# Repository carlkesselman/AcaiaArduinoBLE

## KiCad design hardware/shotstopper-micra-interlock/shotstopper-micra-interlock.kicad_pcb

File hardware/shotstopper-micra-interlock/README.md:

# ShotStopper Micra Interlock

A replacement for the ShotStopper V3.1 board that gives a La Marzocco Linea
Micra Linea Mini-style brew-by-weight:

- Paddle **on**: the shot starts, and the scale tares and starts its timer.
- Target weight reached: the shot **stops even though the paddle is still on**.
- Paddle **off** at any time: the shot stops, as on a stock machine.
- After an automatic stop, the next shot needs the paddle turned off and on again.
- If the board is unpowered, unplugged from the scale, or crashed, the paddle
  works exactly like a stock Micra.

Status: **design only.** The board has not been built and the firmware has
not run on hardware. Work through [Before you order](#before-you-order) first.

## Same as V3.1

- **Outline and mounting holes**, so it fits the V3.1 case and the same spot in
  the machine.
- **The ESP32-C3 section** at V3.1's pad positions: ESP32-C3-WROOM-02 module
  (antenna over the cut-out), USB-C for power and flashing, BOOT and RESET
  buttons, and the same RGB LED (MEIHUA MHP5050RGBDT) on the same pins (red
  GPIO21, green GPIO20, blue GPIO10), so the indicator colours are unchanged.
- **The connectors and cables.** J3 and J4 are 4-pin headers in the same holes
  V3.1 uses for the Micra (the middle four of the 2x8 pattern's even row, ribbon
  pins 6, 8, 10, 12). The install is the same unplug/plug:
  - **J3 "Buttons"**: the Micra's own paddle plug.
  - **J4 "Brain"**: the black/yellow cable to **CN9** on the control board.
  - **J7 "PWR"**: the red/black cable from **CN4** (+5 V). J7 is turned 90°
    compared with V3.1's power header: pins side by side, + on the left, latch
    wall toward the board edge.

  Pin 1 (square pad, marked BLK) is common, the black wire. Pin 4 is the paddle
  line: the white wire on J3 (marked WHT) and the yellow wire on J4 (marked
  YEL). This is the pin order of the V3.1 Micra kit, checked against V3.1's
  drill file and photos of both sides of a V3.1 board: its 4-pin headers sit
  in the row without the square pad, in holes 3 to 6 counted from the
  square-pad end, with black at hole 3.
  Pins 2 and 3 (CN9 keys the Micra doesn't use) pass straight through.

Removed from V3.1: the Q1 optocoupler ("induce" and "detect"), the SB1–SB5
jumpers, the spade terminals and the reed-switch header. There is no remote
start.

## How it works

Full schematic: [schematic.svg](schematic.svg) (drawn by `schematic.py`; the
netlist itself is in `design.py`).

```
 J3 pin 4 (paddle) ── PADDLE ───[ K1 normally-closed ]─── BRAIN ── J4 pin 4 (to CN9)
                        │
                        └──|<── D4 ── U1 LED ── R10 ── ISO 5V ┐
                                     (R12 across LED)          PS1 isolated DC-DC
 J3/J4 pin 1 (COMMON) ────────────────────────────── ISO 0V ┘   5 V → 5 V
                                                                    (R11 min load)
 GPIO5 ── R1 ── K1 LED            HIGH = K1 open = machine sees paddle off
       └─ R9 10k to GND           keeps K1 closed during boot / reset
 GPIO8 ── U1 transistor to GND    LOW = paddle on  (R13 47k pull-up)
```

- **K1** (CPC1117N) is a normally-closed solid-state switch in series with the
  paddle line. Driving GPIO5 high opens it, so the control board sees the paddle
  as off and stops the shot. With no drive, it is closed.
- **U1** senses the paddle independently of K1. A small isolated 5 V supply
  (PS1) pushes about 1.4 mA through U1's LED and D4 into the paddle wire. When
  the paddle shorts that wire to COMMON, U1 conducts and pulls GPIO8 low. This
  works with K1 open or closed, so the firmware always knows where the paddle is.
- **D4** stops the control board's own pull-up from feeding back into the sense
  circuit. **R10** (2.2 kΩ) sets the sense current and limits what this branch
  could ever push into the control board's input. **R12** (100 kΩ) keeps U1's
  LED off on leakage alone. R12 must stay high: with a low value, a shorted D4
  on an unpowered board would pull the paddle line low through R12, R10 and
  R11, and the machine would brew with the paddle off.
- **R11** (220 Ω, 1206) draws about 21 mA so that PS1 has its 10 % minimum load. With
  less, its output is unspecified and can rise well above 5 V.
- The ESP32 side and the machine side share no copper. They connect only
  through K1, U1 and PS1. The minimum copper gap between the two sides is
  0.8 mm (between PS1's own pins). That is **functional isolation for a
  low-voltage paddle line, not mains-rated isolation.**
- Power: 5 V from CN4 comes in through a resettable fuse (F1, 0.5 A) and D5,
  and USB 5 V through D1. Neither source back-feeds the other, a reversed J7
  does no damage, and a fault on this board cannot draw more than the fuse
  allows from the machine's supply. The shared rail (about 4.6 V) feeds the
  3.3 V regulator (U2).
- PS1 (B0505S-1WR3, 5 V in, 5 V out) is fed from J7 only, through D6. **On USB
  power alone the paddle sensing is off**, so the board can never drive the
  control board's paddle input while the machine is off. PS1 is not on the
  3.3 V rail, which keeps its load, and heat, off the small regulator.
- **D7** (6.2 V zener) clamps the isolated rail in case PS1 ever runs unloaded.

### What the machine's control board sees

- Paddle off: the sense circuit is behind D4, which is reverse-biased by the
  control board's own 5 V pull-up, so nothing flows into or out of the paddle
  input. The isolated rail (4.6–5.5 V, 6.5 V at most with D7) minus D4's drop
  stays at or below the control board's 5 V in normal operation; at the top of
  that range a few microamps can flow through R12 (under 30 mV on a 10 k
  pull-up).
- Paddle on: the sense current (about 1.4 mA) flows from PS1 through the paddle
  switch and back to PS1 on this board. None of it flows in the CN9 cable.
- K1 adds at most 16 Ω in series (8 mV at the measured 0.5 mA) when closed and
  about 1 µA of leakage when open.
- Board unpowered or J7 unplugged: PS1 is off, D4 blocks, K1 is closed. The
  paddle line is as on a stock machine.
- Extra load on CN4: PS1 draws about 35-40 mA from the machine's 5 V, on top
  of the ESP32's draw that V3.1 already has (about 125-140 mA in total, with
  peaks near 400 mA only during WiFi updates).

### If something on this board fails

Worked through for every part (open and short). What the machine can see:

| Fault | Effect on the machine |
|---|---|
| K1 fails open, or GPIO5 stuck high | Never brews until fixed or the board is bypassed. Nothing is damaged |
| K1 fails shorted, K1 drive open | No automatic stop; the paddle still starts and stops |
| U1, R10 or D4 open | No paddle sensing: stock behaviour, no automatic stop |
| R13 open | None: the firmware also enables the ESP32's internal pull-up on GPIO8 |
| U1's output shorted, GPIO8 stuck low | Firmware sees "paddle on" for ever, stops at 90 s and holds: never brews |
| D4 shorted | Board powered: no effect. Board unpowered: input stays above 4.5 V (R12), no brew |
| R11 open | Isolated rail rises to D7's 6.2-6.6 V; at most about 40 µA reaches the input, under 5.4 V |
| C3, C8 or PS1 shorted | F1 limits the current from CN4; the board goes dead, the machine behaves as stock |
| J4 header or cable fitted reversed | **Machine brews as soon as it is powered**, and about 0.6 mA is pulled out of the input. Caught by the bench check below, before the board goes in |
| J3 and J4 plugs swapped | Works by hand; the first automatic stop restarts within 0.3 s, the firmware detects it and disables the interlock (fast white blink) |
| J7 fitted reversed | Board dead (D5, D6 block). Do not connect USB in that state |

The control board's input circuit is not known. Limits above are for an input
with protection diodes to its 5 V and ground, or behind a series resistor.

GPIO8 is V3.1's "IN" pin. V3.1's "OUT" (GPIO6, remote start) is not connected.

GPIO8 is also an ESP32-C3 boot-mode pin: to enter the bootloader with the BOOT
button, have the paddle **off**. Normal start-up is not affected.

## Firmware

Build and flash with PlatformIO from the repo root: `pio run -t upload` (the
`micra` environment sets `MOMENTARY false` and `PADDLE_INTERLOCK true` for the
ESP32-C3). In the Arduino IDE, set those two in
`examples/shotStopper/shotStopper.ino` and pick an ESP32-C3 board with
"USB CDC On Boot" enabled.

What the firmware does in this mode:

| Event | Result |
|-------|--------|
| Paddle on | Machine brews; the shot is tracked: tare, reset and start the timer |
| Predicted target weight, or `MAX_SHOT_DURATION_S` | GPIO5 high: K1 opens and the shot stops |
| Paddle still on after the stop | K1 stays open; no new shot |
| Paddle off for 0.3 s (`PADDLE_DEBOUNCE_MS`) | GPIO5 low: K1 closes, so the next paddle-on always brews. Done from a 5 ms timer, so it does not wait for Bluetooth |
| Paddle off before the target | Shot stops; K1 never opens |
| Scale lost during a weighed shot | GPIO5 high: the shot stops (`STOP_ON_SCALE_LOSS`; set it `false` to leave the shot to the paddle) |
| Scale not connected when the paddle goes on | K1 stays closed; the paddle works by hand |
| Paddle on for `INTERLOCK_MAX_BREW_S` (90 s), with or without a scale | GPIO5 high: the brew stops until the paddle is off |
| Cup lifted or scale knocked for 5 s during a weighed shot (`READINGS_LOST_S`) | Treated like a lost scale: the shot stops |
| Scale connects partway through a shot | Within 5 s of paddle-on the shot is tared and weighed; later than that it is left to the paddle |
| Crash or watchdog reset during a held stop | K1 closes for the fraction of a second the ESP32 takes to restart (the machine may click on briefly), then the stop is held again until the paddle is off |
| Crash or watchdog reset during a weighed shot | The shot is stopped at restart and held until the paddle is off: nothing is weighing it any more |
| Board keeps resetting with the paddle on | The 90 s limit counts across resets |
| `loop()` stalls for 20 s (`WATCHDOG_S`) | The watchdog resets the board. A held stop is still released by the timer meanwhile |
| Paddle reads off right after a stop, then on again | Plugs look swapped: interlock disabled until restart, fast white blink |

### Fail-safe guarantees

- **Paddle off always stops brewing.** This is enforced by hardware: K1 is in
  series, so an open paddle opens the line whatever the ESP32 does.
- **Board unpowered, unplugged, or held in reset.** K1 is normally closed, and R9
  keeps it closed while GPIO5 is undriven, so the Micra behaves as stock.
- **Paddle on starts brewing** whenever the firmware is running, or the board is
  off or resetting. The only time it doesn't is an automatic stop being held,
  and that hold ends once the paddle has read off for 0.3 s. The release runs
  from a timer, independently of `loop()`, so a stalled Bluetooth call cannot
  delay it; a hung `loop()` is reset by the watchdog within `WATCHDOG_S`.
  After an automatic stop, leave the paddle off for at least a third of a
  second before turning it on again.
- **An automatic stop opens K1 first**, before any Bluetooth traffic or
  logging, so a failed link cannot delay it.
- **No remote start.** The ESP32 can only interrupt the paddle line. It cannot
  make the machine brew.

These cases are covered by host tests (`tests/interlock/run.sh`: the real
sketch and library against stub Arduino and Bluetooth headers, 30 scripted
scenarios), not on hardware.

Flow rate, the scale sanity checks and over-the-air updates are described
in [`examples/shotStopper/README.md`](../../examples/shotStopper/README.md).

## Ordering from PCBWay

Everything is in `fab/`:

| File | Upload as |
|------|-----------|
| `shotstopper-micra-interlock-gerbers.zip` | PCB Gerber files (includes drill files) |
| `bom.csv` | Assembly BOM (manufacturer part numbers) |
| `centroid.csv` | Pick-and-place / centroid file (mm, top side) |

PCB options: 2 layers, 51.9 × 41.3 mm, 1.6 mm FR-4, 1 oz copper, any
solder-mask colour, lead-free HASL or ENIG. Minimum track 0.15 mm (the USB-C
signals only; 0.25 mm elsewhere), minimum gap 0.2 mm, smallest drill 0.3 mm
(vias), all inside PCBWay's standard capability.

Assembly: top side only, SMD plus four through-hole parts (the J3, J4, J7
headers and PS1).

## Before you order

1. **Headers.** J3 and J4 are TE AMPMODU MOD II 280371-1 (4-pin) and J7 is
   280370-1 (2-pin): 2.54 mm, partially shrouded, with a latch window. The
   V3.1 seller's cable plugs are the matching MOD II housings (280359 4-pin,
   280358 2-pin), and the listed header bodies (12.7 x 5 mm, 7.7 x 5 mm) match
   those measured on V3.1. Per AMP drawing C-280370 the body is 5.0 mm wide
   and 12.6 mm tall, with the pin row 2.2 mm from one face and 2.8 mm from the
   other; the 5.8 mm outlines on the board cover either way round, and J7
   clears R10/R12 and the board edge by at least 0.4 mm in both cases. The
   latch wall goes on the side with the thick silkscreen bar: with the USB
   connector up, on the right for J3 and J4 (as on V3.1) and toward the board
   edge for J7, which is turned 90 degrees. A reversed J7 swaps + and -: red
   goes to the pin marked +.
2. **Paddle line: measured.** On the CN9 cable the control board pulls the
   paddle line up to 5 V DC through about 10 k (5.0 V open, 2.52 V across
   10 k, no AC), so about 0.5 mA flows with the paddle on. The machine does not
   brew at 2.52 V.
3. **Clearance and screws.** PS1 is about 10 mm and the headers 12.6 mm tall;
   the V3.1 case is open on top. At the mounting hole between the headers
   (H2), machine-side copper starts 3.6 mm from the hole centre: use the V3.1
   pan-head screw **without a washer** (or a nylon screw). A metal washer or
   hex standoff there could bridge the paddle line to common, which the
   machine reads as "paddle on".
4. **First power-up on the bench, before the board goes near the machine.**
   - USB only: the LED lights; GPIO5 high makes K1 open (measure the
     resistance between J3 pin 4 and J4 pin 4: a few ohms closed, open when
     high).
   - Then 5 V from a bench supply on J7 (red to +), no USB, with the CN9 cable
     plugged into J4 and its other end free. Measure at that free plug, yellow
     (+) to black: it must be **positive, about 4 to 5.2 V**. Negative means J4
     is fitted backwards: do not connect it.
   - Put 10 k from a second 5 V to the yellow wire (grounds joined at the
     black wire) to imitate the control board: yellow must then read 5.0 V
     with J3 open, and near 0 V with J3 pin 4 shorted to pin 1. GPIO8 goes low
     with that short. Across C9 expect about 4.4 to 5.4 V.
5. **In the machine, first time.** Plug J7 with the machine switched off (PS1
   is not rated for hot-plugging). Check CN4 still reads close to 5 V with the
   board running. If the status LED blinks white fast after the first
   automatic stop, the J3 and J4 plugs are swapped.

PCBWay order form values and assembly notes are in
[ORDER_NOTES.md](ORDER_NOTES.md) (copied into `fab/` with the files to upload).

Work inside the Micra only with it unplugged. Mains is present in the chassis.

## Regenerating the board

`design.py` is the source of truth: parts, positions, nets, and the
logic/machine routing areas.

```bash
./make_all.sh /path/to/python-with-numpy-scipy-pillow
```

The script runs `build_board.py` (KiCad Python: places the parts),
`route.py` (a small two-layer router that keeps each net on its own side),
`finish_board.py` (adds tracks, the ground pour and silkscreen), `set_rules.py`
(design rules), KiCad DRC, and the
Gerber/drill/BOM/centroid exports. It needs KiCad 10. You can open
`shotstopper-micra-interlock.kicad_pcb` in KiCad and edit it by hand, but a
rerun of the script overwrites it.

There is no schematic file. The netlist is in `design.py` (`NETS`).

Based on ShotStopper V3.1 by Tate Mazer (MIT License).

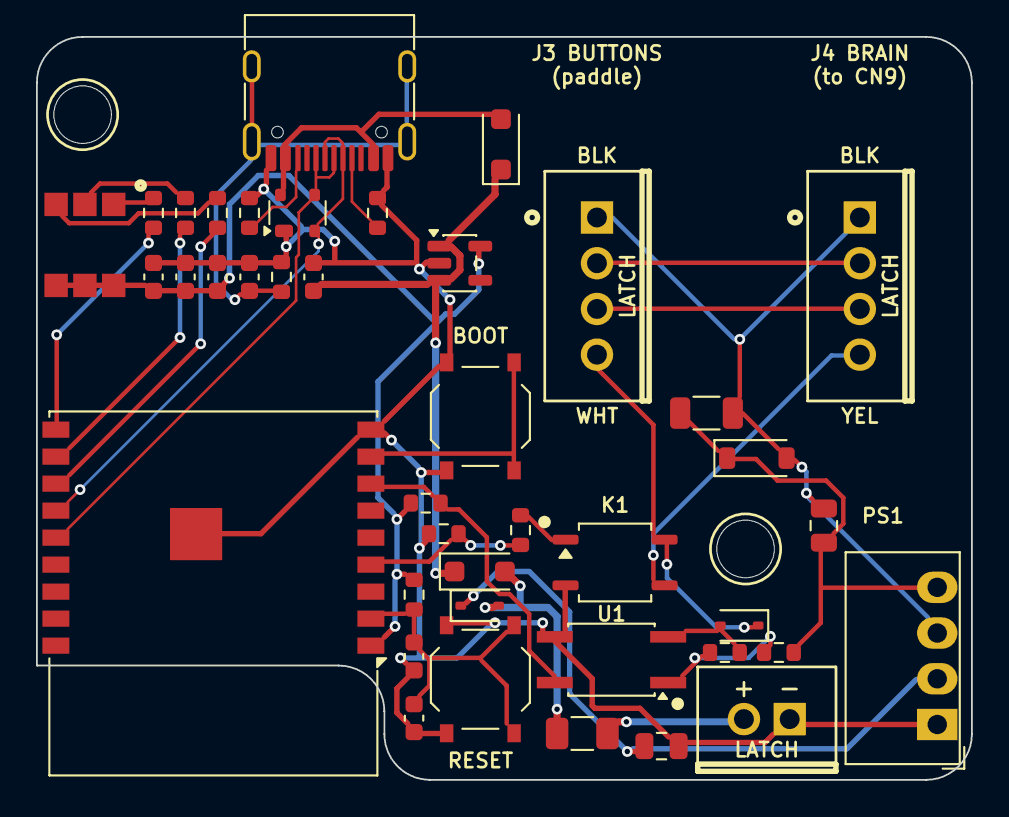
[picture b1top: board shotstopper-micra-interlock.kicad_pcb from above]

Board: 2 copper layers, 51.9 x 41.3 mm, 43 parts (0 on the bottom side), 31 nets.

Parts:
C1: 10u; C_0603_1608Metric
C2, C6: 0.1u; C_0603_1608Metric
C3, C4: 4.7u; C_0603_1608Metric
C5: 1u; C_0603_1608Metric
C7: 4.7n; C_0603_1608Metric
C8: 4.7u; C_0805_2012Metric
C9: 10u; C_0805_2012Metric
D1, D5: PMEG6010CEH; D_SOD-123F
D2: RGB; LED_RGB_5050_MHP
D3: PRTR5V0U2X; SOT-143
D4: 1N4148WS; D_SOD-323
D6: B0520WS; D_SOD-323
D7: 6.2V; D_SOD-123
F1: 0.5A; Fuse_1206_3216Metric
H1, H2: MountingHole_3.2mm_M3_Standoff
J3: Buttons; Header_1x04_Latching
J4: Brain; Header_1x04_Latching
J7: PWR; Header_1x02_Latching
K1: CPC1117N; SOP-4_3.8x4.1mm_P2.54mm
PS1: B0505S-1WR3; Converter_DCDC_Murata_MEE1SxxxxSC_THT
R1: 390; R_0603_1608Metric
R2, R9: 10k; R_0603_1608Metric
R3, R4, R5: 499; R_0603_1608Metric
R6, R7: 5.1k; R_0603_1608Metric
R8: 1M; R_0603_1608Metric
R10: 2.2k; R_0603_1608Metric
R11: 220; R_1206_3216Metric
R12: 100k; R_0603_1608Metric
R13: 47k; R_0603_1608Metric
SW1: BOOT; SW_Push_1P1T_XKB_TS-1187A
SW2: RESET; SW_Push_1P1T_XKB_TS-1187A
U1: EL357N; SO-4_4.4x3.6mm_P2.54mm
U2: TLV75733P; SOT-23-5
U3: ESP32-C3-WROOM-02-N4; ESP32-C3-WROOM-02
USB1: USB-C; USB_C_Receptacle_HRO_TYPE-C-31-M-12

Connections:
+3V3: C1.1, C2.1, C4.1, D2.1, D2.3, D2.5, R2.1, R13.1, U2.5, U3.1
BOOT: SW1.2, U3.8
BRAIN: J4.4, K1.3
CC1: R7.1, USB1.A5
CC2: R6.1, USB1.B5
COMMON: C9.2, D7.2, J3.1, J4.1, PS1.3, R11.2
EN: C5.1, C6.1, R2.2, SW2.2, U3.2
GND: C1.2, C2.2, C3.2, C4.2, C5.2, C6.2, C7.2, C8.2, D3.1, J7.1, K1.2, PS1.1, R6.2, R7.2, R8.2, R9.1, SW1.1, SW2.1, U1.3, U2.2, U3.9, U3.19, USB1.A1, USB1.A12, USB1.B1, USB1.B12
ISO5V: C9.1, D7.1, PS1.4, R10.2, R11.1
K1_A: K1.1, R1.2
KEY2: J3.2, J4.2
KEY3: J3.3, J4.3
LEDK_B: D2.2, R3.2
LEDK_G: D2.4, R4.2
LEDK_R: D2.6, R5.2
LED_B: R3.1, U3.10
LED_G: R4.1, U3.11
LED_R: R5.1, U3.12
PADDLE: D4.1, J3.4, K1.4
SENSE: R13.2, U1.4, U3.7
SHIELD: C7.1, R8.1, USB1.SH
STOP: R1.1, R9.2, U3.4
U1_A: R10.1, R12.1, U1.1
U1_K: D4.2, R12.2, U1.2
USB_DN: D3.2, U3.13, USB1.A7, USB1.B7
USB_DP: D3.3, U3.14, USB1.A6, USB1.B6
VIN: C3.1, D1.1, D5.1, U2.1, U2.3
VIN_F: D5.2, D6.2, F1.1
VIN_J: F1.2, J7.2
VPS: C8.1, D6.1, PS1.2
VUSB: D1.2, D3.4, USB1.A4, USB1.A9, USB1.B4, USB1.B9

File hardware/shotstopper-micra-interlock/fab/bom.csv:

Item,Designator,Qty,Manufacturer,Mfg Part #,Description / Value,Package/Footprint,Type,Notes
1,U3,1,Espressif,ESP32-C3-WROOM-02-N4,"ESP32-C3-WROOM-02-N4 - ESP32-C3 module, 4 MB flash, PCB antenna",ESP32-C3-WROOM-02,SMD,ESP32-C3-WROOM-02-H4 is an acceptable alternate
2,USB1,1,HRO,TYPE-C-31-M-12,USB-C - USB-C receptacle (power + programming),USB_C_Receptacle_HRO_TYPE-C-31-M-12,SMD,SMD pads reflow; the four shell tabs are plated slots without paste: hand solder them
3,U2,1,Texas Instruments,TLV75733PDBVR,TLV75733P - LDO 3.3 V 1 A,SOT-23-5,SMD,
4,"D1,D5",2,Nexperia,"PMEG6010CEH,115",PMEG6010CEH - Schottky 60 V 1 A: USB 5 V into VIN,D_SOD-123F,SMD,
5,D2,1,MEIHUA,MHP5050RGBDT,"RGB - RGB LED 5050 (LCSC C409780, as V3.1); anodes 1/3/5, cathodes 2 B, 4 G, 6 R",LED_RGB_5050_MHP,SMD,Source by LCSC C409780. Cathode mark (pin 2 corner) at the silkscreen dot
6,D3,1,Nexperia,"PRTR5V0U2X,215",PRTR5V0U2X - USB ESD protection,SOT-143,SMD,
7,"SW1,SW2",2,XKB,TS-1187A-B-A-B,"BOOT / RESET - Tactile switch (boot, GPIO9)",SW_Push_1P1T_XKB_TS-1187A,SMD,Source by LCSC C318884
8,C1,1,Samsung,CL10A106KP8NNNC,10uF 10V X5R 20% 0603 ceramic capacitor,C_0603_1608Metric,SMD,any equivalent value/size/rating from a major maker is acceptable
9,"C2,C6",2,Samsung,CL10B104KB8NNNC,0.1uF 50V X7R 10% 0603 ceramic capacitor,C_0603_1608Metric,SMD,any equivalent value/size/rating from a major maker is acceptable
10,"C3,C4",2,Samsung,CL10A475KO8NNNC,4.7uF 16V X5R 10% 0603 ceramic capacitor,C_0603_1608Metric,SMD,any equivalent value/size/rating from a major maker is acceptable
11,C5,1,Samsung,CL10A105KB8NNNC,1uF 50V X5R 10% 0603 ceramic capacitor,C_0603_1608Metric,SMD,any equivalent value/size/rating from a major maker is acceptable
12,C7,1,Samsung,CL10B472KB8NNNC,4.7nF 50V X7R 10% 0603 ceramic capacitor,C_0603_1608Metric,SMD,any equivalent value/size/rating from a major maker is acceptable
13,"R2,R9",2,Yageo,RC0603FR-0710KL,10k ohm 1% 0603 thick-film resistor,R_0603_1608Metric,SMD,any equivalent value/size/rating from a major maker is acceptable
14,"R3,R4,R5",3,Yageo,RC0603FR-07499RL,499 ohm 1% 0603 thick-film resistor,R_0603_1608Metric,SMD,any equivalent value/size/rating from a major maker is acceptable
15,"R6,R7",2,Yageo,RC0603FR-075K1L,5.1k ohm 1% 0603 thick-film resistor,R_0603_1608Metric,SMD,any equivalent value/size/rating from a major maker is acceptable
16,R8,1,Yageo,RC0603FR-071ML,1M ohm 1% 0603 thick-film resistor,R_0603_1608Metric,SMD,any equivalent value/size/rating from a major maker is acceptable
17,"J3,J4",2,TE Connectivity,280371-1,Buttons / Brain - 1x4 2.54 mm latching header: paddle plug,Header_1x04_Latching,Thru-hole,"Through-hole, hand solder. Pin 1 = square pad; latch (solid) wall on the side marked LATCH / thick silkscreen bar"
18,J7,1,TE Connectivity,280370-1,"PWR - 1x2 2.54 mm latching header: 5 V from CN4 (1 = GND, 2 = +5 V)",Header_1x02_Latching,Thru-hole,"Through-hole, hand solder. latch (solid) wall on the side marked LATCH / thick silkscreen bar (toward the board edge); reversed = + and - swapped"
19,K1,1,Littelfuse,CPC1117NTR,CPC1117N - OptoMOS relay 1-Form-B (normally closed) 60V 150mA,SOP-4_3.8x4.1mm_P2.54mm,SMD,Normally-CLOSED (1-Form-B) type: NO SUBSTITUTION. Pin 1 at the silkscreen dot
20,U1,1,Everlight,EL357N(C)(TA)-G,"EL357N - Optocoupler, paddle sense",SO-4_4.4x3.6mm_P2.54mm,SMD,Pin 1 at the silkscreen dot (part is turned 180 degrees)
21,PS1,1,Mornsun,B0505S-1WR3,B0505S-1WR3 - Isolated DC-DC 5V->5V 1W SIP-4,Converter_DCDC_Murata_MEE1SxxxxSC_THT,Thru-hole,"Through-hole SIP-4, hand solder (no reflow). Pin 1 = square pad"
22,D6,1,Diodes Inc,B0520WS-7-F,B0520WS - Schottky 20 V 0.5 A: J7 5 V into PS1,D_SOD-323,SMD,
23,F1,1,Bourns,MF-NSMF050-2,0.5A - Resettable fuse 0.5 A hold / 1 A trip: J7 input,Fuse_1206_3216Metric,SMD,"Any 1206 PPTC with 0.5 A hold, 1 A trip, >= 6 V is acceptable"
24,D7,1,onsemi,MMSZ5234BT1G,6.2V - Zener 6.2 V 500 mW: isolated rail clamp,D_SOD-123,SMD,
25,D4,1,Diodes Inc,1N4148WS-7-F,1N4148WS - Signal diode,D_SOD-323,SMD,
26,R1,1,Yageo,RC0603FR-07390RL,390 ohm 1% 0603 thick-film resistor,R_0603_1608Metric,SMD,any equivalent value/size/rating from a major maker is acceptable
27,R10,1,Yageo,RC0603FR-072K2L,2.2k ohm 1% 0603 thick-film resistor,R_0603_1608Metric,SMD,any equivalent value/size/rating from a major maker is acceptable
28,R11,1,Yageo,RC1206FR-07220RL,220 ohm 1% 1206 0.25W thick-film resistor,R_1206_3216Metric,SMD,any equivalent value/size/rating from a major maker is acceptable
29,R12,1,Yageo,RC0603FR-07100KL,100k ohm 1% 0603 thick-film resistor,R_0603_1608Metric,SMD,any equivalent value/size/rating from a major maker is acceptable
30,R13,1,Yageo,RC0603FR-0747KL,47k ohm 1% 0603 thick-film resistor,R_0603_1608Metric,SMD,any equivalent value/size/rating from a major maker is acceptable
31,C8,1,Samsung,CL21A475KAQNNNE,4.7uF 25V X5R 10% 0805 ceramic capacitor,C_0805_2012Metric,SMD,any equivalent value/size/rating from a major maker is acceptable
32,C9,1,Samsung,CL21A106KAYNNNE,10uF 25V X5R 10% 0805 ceramic capacitor,C_0805_2012Metric,SMD,any equivalent value/size/rating from a major maker is acceptable

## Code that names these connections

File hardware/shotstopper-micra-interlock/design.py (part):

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
# --- Machine connectors: one 1x4 latching header each, in the middle four holes of
# the even row of V3.1's 2x8 pattern, where V3.1 fits them for the Micra. Header
# pin 1 = V3.1 ribbon pin 6 (common, black wire), pin 4 = ribbon pin 12 (paddle).
# J3 "Buttons": the paddle's own plug.  J4 "Brain": the cable to CN9.
J3_PIN1 = g(99.06, 86.487)
J4_PIN1 = g(113.665, 86.487)
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    "R7": ("5.1k", R0603, "RC0603FR-075K1L", "Yageo", "USB CC pull-down", v31(86.868, 86.741, 90)),
    "R8": ("1M", R0603, "RC0603FR-071ML", "Yageo", "USB shield to GND", v31(81.534, 83.185, 90)),
    # ---- connectors ----
    "J3": ("Buttons", HDR4, LATCH4_MPN, "TE Connectivity", "1x4 2.54 mm latching header: paddle plug", J3_PIN1 + (0,)),
    "J4": ("Brain", HDR4, LATCH4_MPN, "TE Connectivity", "1x4 2.54 mm latching header: cable to CN9", J4_PIN1 + (0,)),
    "J7": ("PWR", HDR2, LATCH2_MPN, "TE Connectivity", "1x2 2.54 mm latching header: 5 V from CN4 (1 = GND, 2 = +5 V)",
           PWR_PIN1 + (PWR_ROT,)),
    # ---- interlock section ----
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             ("D2", "1"), ("D2", "3"), ("D2", "5"), ("R13", "1")],
    "VIN": [("D5", "1"), ("D1", "1"), ("U2", "1"), ("U2", "3"), ("C3", "1")],
    "VUSB": USB_VBUS + [("D1", "2"), ("D3", "4")],
    "USB_DP": [("USB1", "A6"), ("USB1", "B6"), ("D3", "3"), ("U3", "14")],   # GPIO19
    "USB_DN": [("USB1", "A7"), ("USB1", "B7"), ("D3", "2"), ("U3", "13")],   # GPIO18
    "CC1": [("USB1", "A5"), ("R7", "1")],
    "CC2": [("USB1", "B5"), ("R6", "1")],
    "SHIELD": [("USB1", "SH"), ("R8", "1"), ("C7", "1")],
    "EN": [("U3", "2"), ("R2", "2"), ("C5", "1"), ("C6", "1"), ("SW2", "2")],
    "BOOT": [("U3", "8"), ("SW1", "2")],                                     # GPIO9
    "LED_B": [("U3", "10"), ("R3", "1")],                                    # GPIO10
    "LED_G": [("U3", "11"), ("R4", "1")],                                    # GPIO20
    "LED_R": [("U3", "12"), ("R5", "1")],                                    # GPIO21
    "LEDK_B": [("R3", "2"), ("D2", "2")],
    "LEDK_G": [("R4", "2"), ("D2", "4")],
    "LEDK_R": [("R5", "2"), ("D2", "6")],
    "STOP": [("U3", "4"), ("R1", "1"), ("R9", "2")],                         # GPIO5: HIGH opens K1
    "K1_A": [("R1", "2"), ("K1", "1")],
    "SENSE": [("U3", "7"), ("R13", "2"), ("U1", "4")],                       # GPIO8: LOW = paddle on
    # ---- machine side (isolated, referenced to COMMON) ----
    "ISO5V": [("PS1", "4"), ("R10", "2"), ("R11", "1"), ("C9", "1"), ("D7", "1")],
    "COMMON": [("PS1", "3"), ("R11", "2"), ("C9", "2"), ("D7", "2"), ("J3", "1"), ("J4", "1")],
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    "U1_K": [("U1", "2"), ("R12", "2"), ("D4", "2")],
    "PADDLE": [("D4", "1"), ("K1", "4"), ("J3", "4")],
    "BRAIN": [("K1", "3"), ("J4", "4")],
    "KEY2": [("J3", "2"), ("J4", "2")],     # CN9 pins the Micra doesn't use: straight through
    "KEY3": [("J3", "3"), ("J4", "3")],
}
MACHINE_NETS = {"ISO5V", "COMMON", "U1_A", "U1_K", "PADDLE", "BRAIN", "KEY2", "KEY3"}
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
